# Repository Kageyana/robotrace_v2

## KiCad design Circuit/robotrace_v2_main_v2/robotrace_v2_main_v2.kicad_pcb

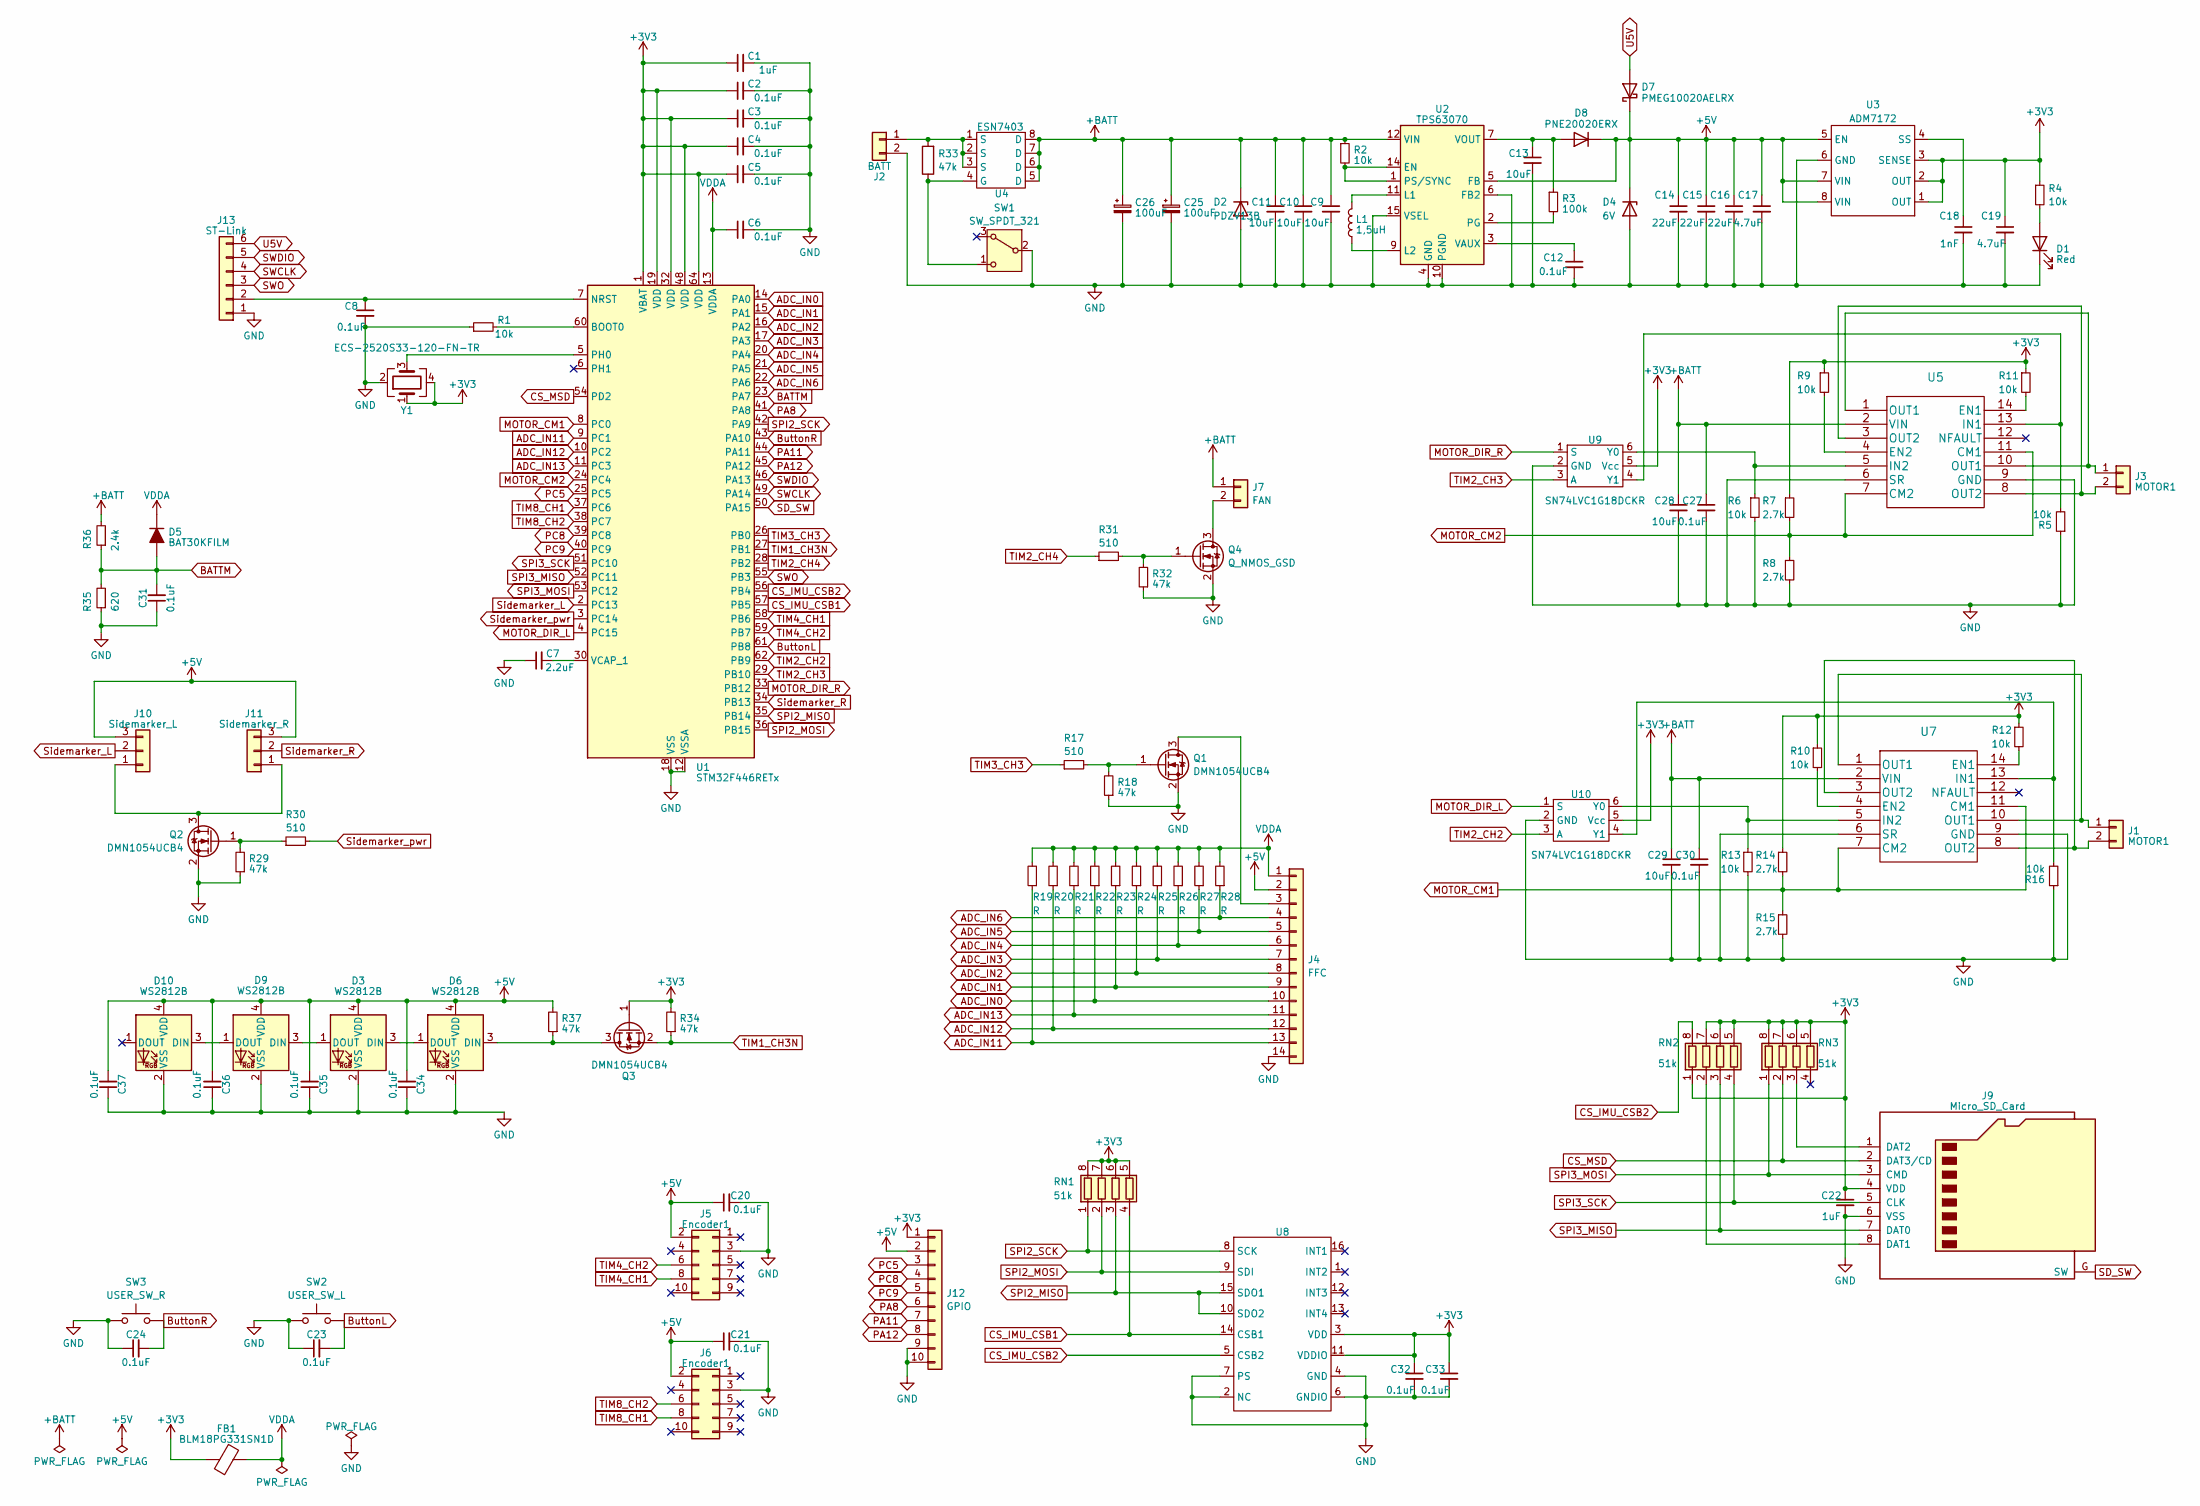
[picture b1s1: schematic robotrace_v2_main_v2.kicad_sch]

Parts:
C1, C22: 1uF; C_0402_1005Metric
C2, C3, C4, C5, C6, C8, C12, C20, C21, C23, C24, C27, C30, C31, C32, C33, C34, C35, C36, C37: 0.1uF; C_0402_1005Metric
C7: 2.2uF; C_0402_1005Metric_Pad0.74x0.62mm_HandSolder
C9, C10, C11: 10uF; C_0603_1608Metric_Pad1.08x0.95mm_HandSolder
C13: 10uF; C_0402_1005Metric
C14, C15, C16: 22uF; C_0805_2012Metric
C17, C19: 4.7uF; C_0402_1005Metric
C18: 1nF; C_0402_1005Metric
C25, C26: 100uF; CP_EIA-7343-15_Kemet-W
C28, C29: 10uF; C_0603_1608Metric
D1: Red; LED_0603_1608Metric_Pad1.05x0.95mm_HandSolder
D2: PDZV13B; D_SOD-128
D3, D6, D9, D10: WS2812B; WS2812C-2020
D4: 6V; D_SOD-123F
D5: BAT30KFILM; D_SOD-523
D7: PMEG10020AELRX; D_SOD-123W
D8: PNE20020ERX; D_SOD-123W
FB1: BLM18PG331SN1D; D_0603_1608Metric_Pad1.05x0.95mm_HandSolder
J1, J3: MOTOR1; Molex_mini-SPOX_1x02_P2.54mm_Horizontal
J2: BATT; Molex_mini-SPOX_1x02_P2.54mm_Horizontal
J4: FFC; Molex_FFC_1x14_P0.50mm_Horizontal
J5, J6: Encoder1; FTSH-105-01-F-D-K
J7: FAN; Molex_mini-SPOX_1x02_P2.54mm_Horizontal
J9: Micro_SD_Card; TF-SMD_TF-06A
J10: Sidemarker_L; JST_SH_BM03B-SRSS-TB_1x03-1MP_P1.00mm_Vertical
J11: Sidemarker_R; JST_SH_BM03B-SRSS-TB_1x03-1MP_P1.00mm_Vertical
J12: GPIO; Molex_FFC_1x10_P0.50mm_Horizontal
J13: ST-Link; JST_SH_BM06B-SRSS-TB_1x06-1MP_P1.00mm_Vertical
L1: 1,5uH; DFE252012P
Q1, Q2, Q3: DMN1054UCB4
Q4: Q_NMOS_GSD; SOT-23
R1, R2, R4: 10k; R_0402_1005Metric
R3: 100k; R_0402_1005Metric
R5, R6, R9, R10, R11, R12, R13, R16: 10k; R_0201_0603Metric
R7, R8, R14, R15: 2.7k; R_0402_1005Metric
R17, R30: 510; R_0201_0603Metric
R18, R29: 47k; R_0201_0603Metric
R19, R20, R21, R22, R23, R24, R25, R26, R27, R28: R; R_0603_1608Metric
R31: 510; R_0402_1005Metric
R32, R33, R34, R37: 47k; R_0402_1005Metric
R35: 620; R_0402_1005Metric
R36: 2.4k; R_0402_1005Metric
RN1, RN2, RN3: 51k; R_Array_Concave_4x0603
SW1: SW_SPDT_321; SS-1290
SW2: USER_SW_L; SKRPABE010
SW3: USER_SW_R; SKRPABE010
U1: STM32F446RETx; LQFP-64_10x10mm_P0.5mm
U2: TPS63070; Texas_TPS63070RNMR_EP2.6x3.1mm
U3: ADM7172; DFN-8_L3.0-W3.0-P0.50-BL-EP
U4: ESN7403; PDFN3x3-8L
U5, U7: MP6551GQB-P
U8: BMI088
U9, U10: SN74LVC1G18DCKR; Texas_R-PDSO-G6
Y1: ECS-2520S33-120-FN-TR; Oscillators_SMD_2.0x1.6

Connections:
+3V3: C1.1, C2.1, C3.1, C4.1, C5.1, C19.1, C22.1, C32.1, C33.1, FB1.2, J9.4 (VDD), J12.1, Q3.1 (G), R4.1, R7.1, R9.1, R10.1, R11.1, R12.1, R14.1, R34.2, RN1.5 (R4.2), RN1.6 (R3.2), RN1.7 (R2.2), RN1.8 (R1.2), RN2.1 (R1.1), RN2.5 (R4.2), RN2.6 (R3.2), RN2.7 (R2.2), RN3.5 (R4.2), RN3.6 (R3.2), RN3.7 (R2.2), RN3.8 (R1.2), U1.1 (VBAT), U1.19 (VDD), U1.32 (VDD), U1.48 (VDD), U1.64 (VDD), U3.1 (OUT), U3.2 (OUT), U3.3 (SENSE), U8.3 (VDD), U8.11 (VDDIO), U9.5 (Vcc), U10.5 (Vcc), Y1.1, Y1.4
+5V: C14.1, C15.1, C16.1, C17.1, C20.1, C21.1, C34.2, C35.2, C36.2, C37.2, D3.4 (VDD), D4.1 (K), D6.4 (VDD), D7.1 (K), D8.1 (K), D9.4 (VDD), D10.4 (VDD), J4.2, J5.2, J6.2, J10.3, J11.3, J12.2, R37.2, U2.5 (FB), U3.5 (EN), U3.7 (VIN), U3.8 (VIN)
+BATT: C9.1, C10.1, C11.1, C25.1, C26.1, C27.1, C28.1, C29.1, C30.1, D2.1 (K), J7.1, R2.1, R36.2, U2.12 (VIN), U2.13, U4.5 (D), U4.6 (D), U4.7 (D), U4.8 (D), U5.2 (VIN), U7.2 (VIN)
ADC_IN0: J4.10, R22.1, U1.14 (PA0)
ADC_IN1: J4.9, R23.1, U1.15 (PA1)
ADC_IN2: J4.8, R24.1, U1.16 (PA2)
ADC_IN3: J4.7, R25.1, U1.17 (PA3)
ADC_IN4: J4.6, R26.1, U1.20 (PA4)
ADC_IN5: J4.5, R27.1, U1.21 (PA5)
ADC_IN6: J4.4, R28.1, U1.22 (PA6)
ADC_IN11: J4.13, R19.1, U1.9 (PC1)
ADC_IN12: J4.12, R20.1, U1.10 (PC2)
ADC_IN13: J4.11, R21.1, U1.11 (PC3)
BATTM: C31.2, D5.2 (A), R35.2, R36.1, U1.23 (PA7)
ButtonL: C23.2, SW2.2, U1.61 (PB8)
ButtonR: C24.2, SW3.2, U1.43 (PA10)
CS_IMU_CSB1: RN1.4 (R4.1), U1.57 (PB5), U8.14 (CSB1)
CS_IMU_CSB2: RN2.8 (R1.2), U1.56 (PB4), U8.5 (CSB2)
CS_MSD: J9.2 (DAT3/CD), RN3.2 (R2.1), U1.54 (PD2)
GND: C1.2, C2.2, C3.2, C4.2, C5.2, C6.2, C7.1, C8.2, C9.2, C10.2, C11.2, C12.2, C13.2, C14.2, C15.2, C16.2, C17.2, C18.2, C19.2, C20.2, C21.2, C22.2, C23.1, C24.1, C25.2, C26.2, C27.2, C28.2, C29.2, C30.2, C31.1, C32.2, C33.2, C34.1, C35.1, C36.1, C37.1, D1.1 (K), D2.2 (A), D3.2 (VSS), D4.2 (A), D6.2 (VSS), D9.2 (VSS), D10.2 (VSS), J2.2, J4.14, J5.3, J6.3, J9.6 (VSS), J12.9, J12.10, J13.1, Q1.2 (S), Q2.2 (S), Q4.2 (S), R1.1, R5.1, R6.2, R8.2, R13.2, R15.2, R16.1, R18.1, R29.1, R32.1, R35.1, SW1.2 (B), SW2.1, SW3.1, U1.12 (VSSA), U1.18 (VSS), U1.31 (VSS), U1.47 (VSS), U1.63 (VSS), U2.4 (GND), U2.6 (FB2), U2.10 (PGND), U2.15 (VSEL), U3.6 (GND), U3.9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
MOTOR_CM1: R14.2, R15.1, U1.8 (PC0), U7.7 (CM2), U7.11 (CM1)
MOTOR_CM2: R7.2, R8.1, U1.24 (PC4), U5.7 (CM2), U5.11 (CM1)
MOTOR_DIR_L: U1.4 (PC15), U10.1 (S)
MOTOR_DIR_R: U1.33 (PB12), U9.1 (S)
unnamed: D1.2 (A), R4.2
unnamed: D3.3 (DIN), D6.1 (DOUT)
unnamed: D3.1 (DOUT), D9.3 (DIN)
unnamed: D6.3 (DIN), Q3.3 (D), R37.1
unnamed: C13.1, D8.2 (A), R3.1, U2.7 (VOUT), U2.8
unnamed: D9.1 (DOUT), D10.3 (DIN)
unnamed: J1.1, U7.1 (OUT1), U7.10 (OUT1)
unnamed: J1.2, U7.3 (OUT2), U7.8 (OUT2)
unnamed: J2.1, R33.2, U4.1 (S), U4.2 (S), U4.3 (S)
unnamed: J3.1, U5.1 (OUT1), U5.10 (OUT1)
unnamed: J3.2, U5.3 (OUT2), U5.8 (OUT2)
unnamed: J4.3, Q1.3 (D)
unnamed: J7.2, Q4.3 (D)
unnamed: J9.8 (DAT1), RN2.2 (R2.1)
unnamed: J9.1 (DAT2), RN3.3 (R3.1)
unnamed: J10.1, J11.1, Q2.3 (D)
unnamed: C8.1, J13.2, U1.7 (NRST)
unnamed: Q1.1 (G), R17.2, R18.2
unnamed: Q2.1 (G), R29.2, R30.1
unnamed: Q4.1 (G), R31.2, R32.2
unnamed: R33.1, SW1.1 (C), U4.4 (G)
unnamed: R1.2, U1.60 (BOOT0)
unnamed: U1.5 (PH0), Y1.3
unnamed: C7.2, U1.30 (VCAP_1)
unnamed: R2.2, U2.1 (PS/SYNC), U2.14 (EN)
unnamed: L1.2, U2.11 (L1)
unnamed: L1.1, U2.9 (L2)
unnamed: R3.2, U2.2 (PG)
unnamed: C12.1, U2.3 (VAUX)
unnamed: C18.1, U3.4 (SS)
unnamed: R11.2, U5.14 (EN1)
unnamed: R9.2, U5.4 (EN2)
unnamed: R5.2, U5.13 (IN1), U9.4 (Y1)
unnamed: R6.1, U5.5 (IN2), U9.6 (Y0)
unnamed: R12.2, U7.14 (EN1)
unnamed: R10.2, U7.4 (EN2)
unnamed: R13.1, U7.5 (IN2), U10.6 (Y0)
unnamed: R16.2, U7.13 (IN1), U10.4 (Y1)
PA8: J12.6, U1.41 (PA8)
PA11: J12.7, U1.44 (PA11)
PA12: J12.8, U1.45 (PA12)
PC5: J12.3, U1.25 (PC5)
PC8: J12.4, U1.39 (PC8)
PC9: J12.5, U1.40 (PC9)
SD_SW: J9.G (SW), U1.50 (PA15)
SPI2_MISO: RN1.3 (R3.1), U1.35 (PB14), U8.10 (SDO2), U8.15 (SDO1)
SPI2_MOSI: RN1.2 (R2.1), U1.36 (PB15), U8.9 (SDI)
SPI2_SCK: RN1.1 (R1.1), U1.42 (PA9), U8.8 (SCK)
SPI3_MISO: J9.7 (DAT0), RN2.3 (R3.1), U1.52 (PC11)
SPI3_MOSI: J9.3 (CMD), RN3.1 (R1.1), U1.53 (PC12)
SPI3_SCK: J9.5 (CLK), RN2.4 (R4.1), U1.51 (PC10)
SWCLK: J13.4, U1.49 (PA14)
SWDIO: J13.5, U1.46 (PA13)
SWO: J13.3, U1.55 (PB3)
Sidemarker_L: J10.2, U1.2 (PC13)
Sidemarker_R: J11.2, U1.34 (PB13)
Sidemarker_pwr: R30.2, U1.3 (PC14)
TIM1_CH3N: Q3.2 (S), R34.1, U1.27 (PB1)
TIM2_CH2: U1.62 (PB9), U10.3 (A)
TIM2_CH3: U1.29 (PB10), U9.3 (A)
TIM2_CH4: R31.1, U1.28 (PB2)
TIM3_CH3: R17.1, U1.26 (PB0)
TIM4_CH1: J5.8, U1.58 (PB6)
TIM4_CH2: J5.6, U1.59 (PB7)
TIM8_CH1: J6.8, U1.37 (PC6)
TIM8_CH2: J6.6, U1.38 (PC7)
U5V: D7.2 (A), J13.6
VDDA: C6.1, D5.1 (K), FB1.1, J4.1, R19.2, R20.2, R21.2, R22.2, R23.2, R24.2, R25.2, R26.2, R27.2, R28.2, U1.13 (VDDA)

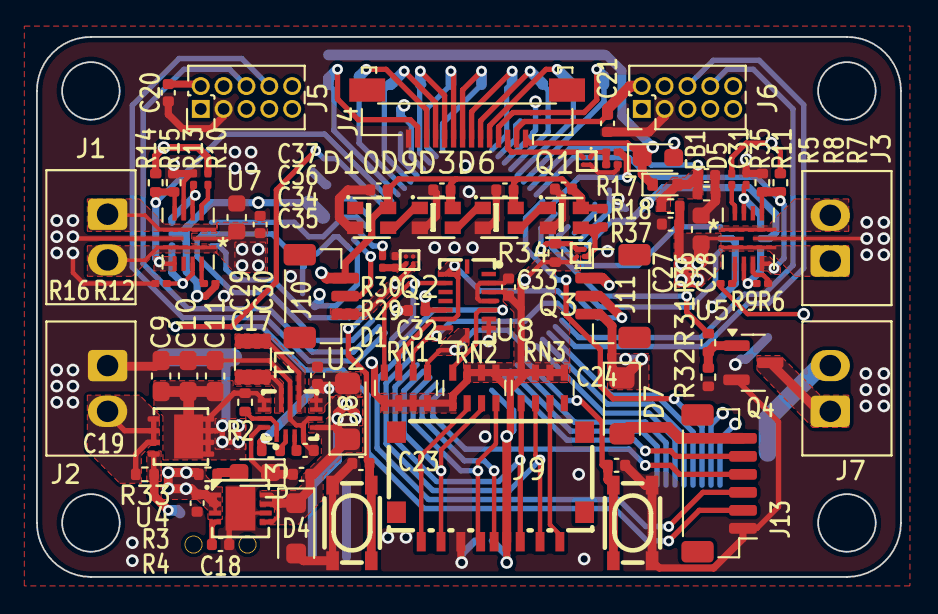
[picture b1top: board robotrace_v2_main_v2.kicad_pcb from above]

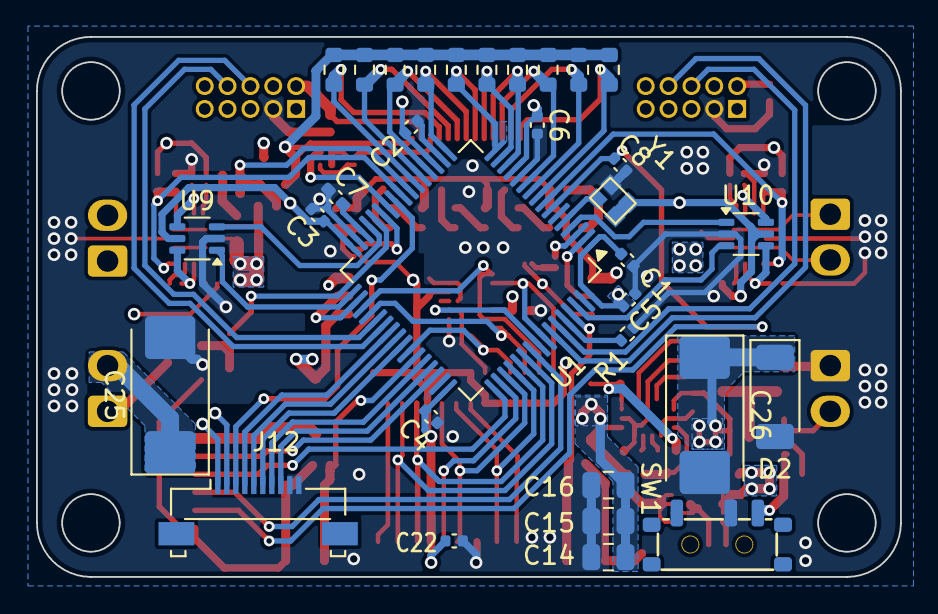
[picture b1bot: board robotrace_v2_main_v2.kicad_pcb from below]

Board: 4 copper layers, 48.0 x 30.0 mm, 118 parts (32 on the bottom side), 92 nets.

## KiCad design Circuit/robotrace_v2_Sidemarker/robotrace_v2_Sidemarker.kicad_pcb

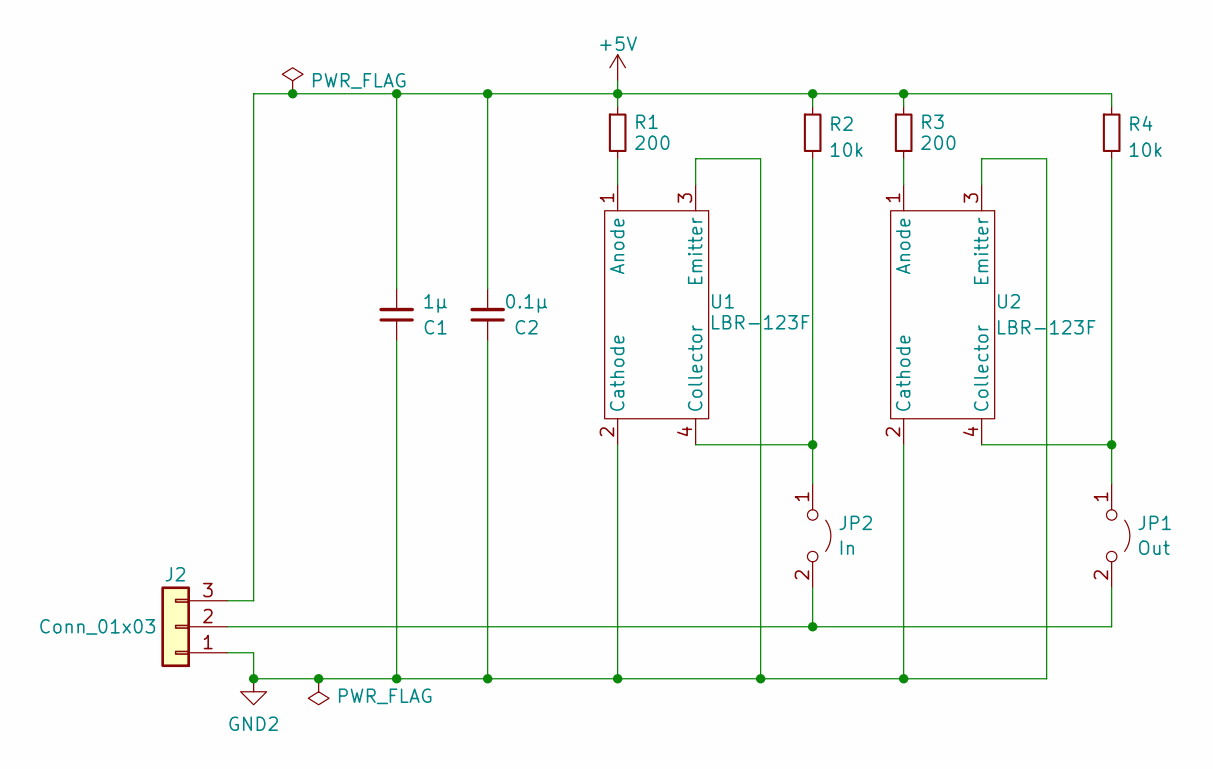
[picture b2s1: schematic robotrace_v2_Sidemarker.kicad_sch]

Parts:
C1: 1μ; C_0402_1005Metric_Pad0.74x0.62mm_HandSolder
C2: 0.1μ; C_0402_1005Metric_Pad0.74x0.62mm_HandSolder
J2: Conn_01x03; PinHeader_1x03_P2.00mm_Vertical
JP1: Out; SolderJumper-2_P1.3mm_Open_TrianglePad1.0x1.5mm
JP2: In; SolderJumper-2_P1.3mm_Open_TrianglePad1.0x1.5mm
R1, R3: 200; R_0603_1608Metric_Pad0.98x0.95mm_HandSolder
R2, R4: 10k; R_0603_1608Metric_Pad0.98x0.95mm_HandSolder
U1, U2: LBR-123F

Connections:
+5V: C1.2, C2.2, J2.3, R1.1, R2.1, R3.1, R4.1
GND2: C1.1, C2.1, J2.1, U1.2 (Cathode), U1.3 (Emitter), U2.2 (Cathode), U2.3 (Emitter)
unnamed: J2.2, JP1.2 (B), JP2.2 (B)
unnamed: JP1.1 (A), R4.2, U2.4 (Collector)
unnamed: JP2.1 (A), R2.2, U1.4 (Collector)
unnamed: R1.2, U1.1 (Anode)
unnamed: R3.2, U2.1 (Anode)

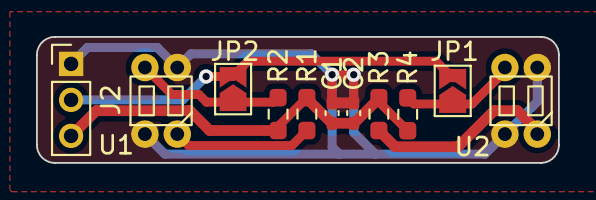
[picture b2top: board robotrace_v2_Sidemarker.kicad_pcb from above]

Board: 2 copper layers, 29.0 x 7.0 mm, 11 parts (0 on the bottom side), 7 nets.

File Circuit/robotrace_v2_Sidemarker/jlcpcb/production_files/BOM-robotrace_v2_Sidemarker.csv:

Comment,Designator,Footprint,LCSC
LBR-123F,U2,LBR-123F,
LBR-123F,U1,LBR-123F,
10k,R4,R_0603_1608Metric_Pad0.98x0.95mm_HandSolder,
200,R3,R_0603_1608Metric_Pad0.98x0.95mm_HandSolder,
Conn_01x03,J2,PinHeader_1x03_P2.00mm_Vertical,
200,R1,R_0603_1608Metric_Pad0.98x0.95mm_HandSolder,
0.1μ,C2,C_0402_1005Metric_Pad0.74x0.62mm_HandSolder,
1μ,C1,C_0402_1005Metric_Pad0.74x0.62mm_HandSolder,
10k,R2,R_0603_1608Metric_Pad0.98x0.95mm_HandSolder,

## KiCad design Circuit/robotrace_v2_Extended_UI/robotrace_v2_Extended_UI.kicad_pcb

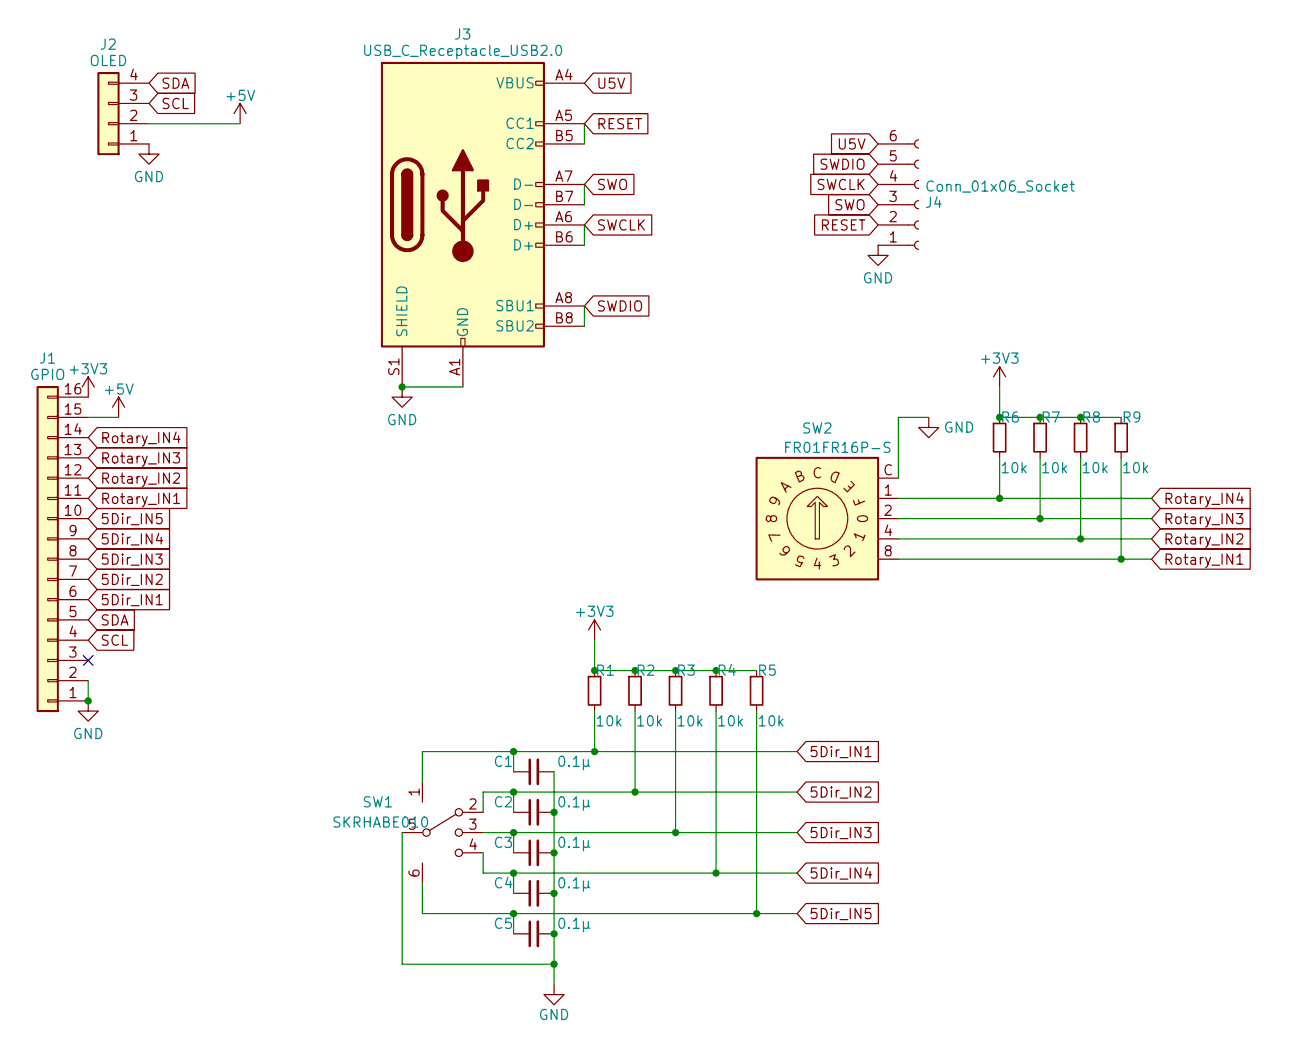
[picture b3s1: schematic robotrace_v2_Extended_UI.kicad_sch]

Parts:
C1, C2, C3, C4, C5: 0.1μ; C_0402_1005Metric_Pad0.74x0.62mm_HandSolder
J1: GPIO; Molex_FFC_1x16_P0.50mm_Horizontal
J2: OLED; PinHeader_1x04_P2.54mm_Vertical
J3: USB_C_Receptacle_USB2.0; USB_C_Receptacle_XKB_U262-16XN-4BVC11
J4: Conn_01x06_Socket; PinHeader_1x06_P1.27mm_Vertical
R1, R2, R3, R4, R5, R6, R7, R8, R9: 10k; R_0603_1608Metric_Pad0.98x0.95mm_HandSolder
SW1: SKRHABE010; SKRHAAE010
SW2: FR01FR16P-S

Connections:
5Dir_IN1: C1.1, J1.6, R1.2, SW1.1
5Dir_IN2: C2.1, J1.7, R2.2, SW1.2
5Dir_IN3: C3.1, J1.8, R3.2, SW1.3
5Dir_IN4: C4.1, J1.9, R4.2, SW1.4
5Dir_IN5: C5.1, J1.10, R5.2, SW1.6
+3V3: J1.16, R1.1, R2.1, R3.1, R4.1, R5.1, R6.1, R7.1, R8.1, R9.1
+5V: J1.15, J2.2
GND: C1.2, C2.2, C3.2, C4.2, C5.2, J1.1, J1.2, J2.1, J3.A1 (GND), J3.A12 (GND), J3.B1 (GND), J3.B12 (GND), J3.S1 (SHIELD), J4.1, SW1.5, SW2.C
RESET: J3.A5 (CC1), J3.B5 (CC2), J4.2
Rotary_IN1: J1.11, R9.2, SW2.8
Rotary_IN2: J1.12, R8.2, SW2.4
Rotary_IN3: J1.13, R7.2, SW2.2
Rotary_IN4: J1.14, R6.2, SW2.1
SCL: J1.4, J2.3
SDA: J1.5, J2.4
SWCLK: J3.A6 (D+), J3.B6 (D+), J4.4
SWDIO: J3.A8 (SBU1), J3.B8 (SBU2), J4.5
SWO: J3.A7 (D-), J3.B7 (D-), J4.3
U5V: J3.A4 (VBUS), J3.A9 (VBUS), J3.B4 (VBUS), J3.B9 (VBUS), J4.6

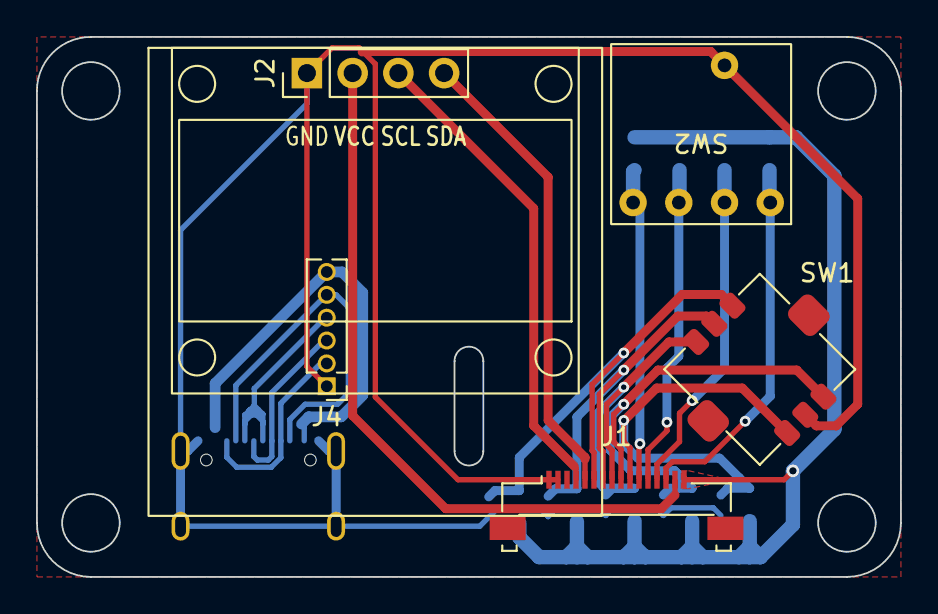
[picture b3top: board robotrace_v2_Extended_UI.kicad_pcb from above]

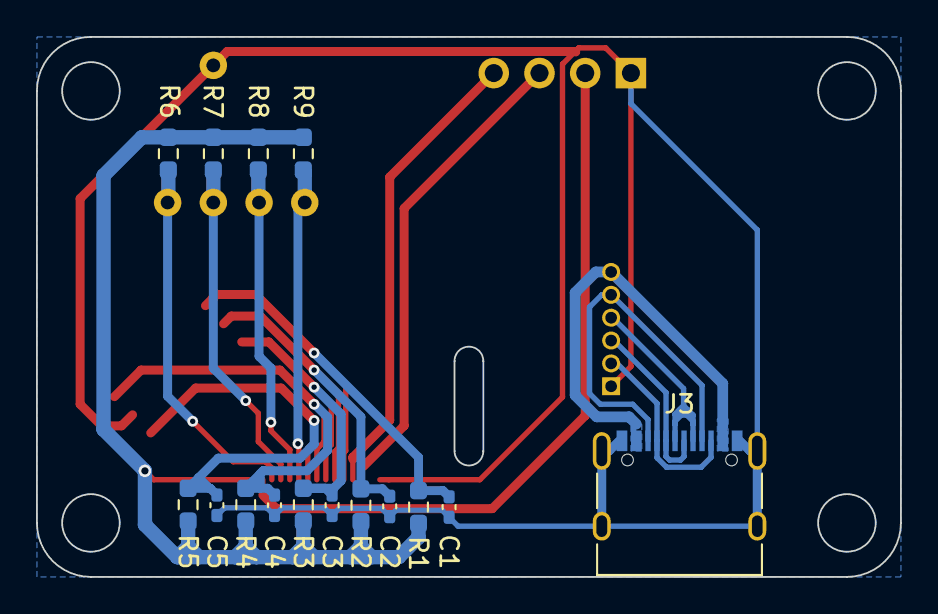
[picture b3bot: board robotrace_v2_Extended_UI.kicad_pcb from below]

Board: 2 copper layers, 48.0 x 30.0 mm, 20 parts (15 on the bottom side), 19 nets.

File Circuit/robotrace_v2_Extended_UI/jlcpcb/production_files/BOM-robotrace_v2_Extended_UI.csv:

Comment,Designator,Footprint,LCSC
OLED,J2,PinHeader_1x04_P2.54mm_Vertical,
GPIO,J1,Molex_FFC_1x16_P0.50mm_Horizontal,
10k,R1,R_0603_1608Metric_Pad0.98x0.95mm_HandSolder,
10k,R9,R_0603_1608Metric_Pad0.98x0.95mm_HandSolder,
10k,R3,R_0603_1608Metric_Pad0.98x0.95mm_HandSolder,
10k,R5,R_0603_1608Metric_Pad0.98x0.95mm_HandSolder,
10k,R8,R_0603_1608Metric_Pad0.98x0.95mm_HandSolder,
0.1μ,C3,C_0402_1005Metric_Pad0.74x0.62mm_HandSolder,
USB_C_Receptacle_USB2.0,J3,USB_C_Receptacle_XKB_U262-16XN-4BVC11,
10k,R7,R_0603_1608Metric_Pad0.98x0.95mm_HandSolder,
0.1μ,C2,C_0402_1005Metric_Pad0.74x0.62mm_HandSolder,
10k,R4,R_0603_1608Metric_Pad0.98x0.95mm_HandSolder,
Conn_01x06_Socket,J4,PinHeader_1x06_P1.27mm_Vertical,
0.1μ,C1,C_0402_1005Metric_Pad0.74x0.62mm_HandSolder,
10k,R2,R_0603_1608Metric_Pad0.98x0.95mm_HandSolder,
0.1μ,C5,C_0402_1005Metric_Pad0.74x0.62mm_HandSolder,
10k,R6,R_0603_1608Metric_Pad0.98x0.95mm_HandSolder,
0.1μ,C4,C_0402_1005Metric_Pad0.74x0.62mm_HandSolder,
SKRHABE010,SW1,SKRHAAE010,
FR01FR16P-S,SW2,FR01FR16P-S,

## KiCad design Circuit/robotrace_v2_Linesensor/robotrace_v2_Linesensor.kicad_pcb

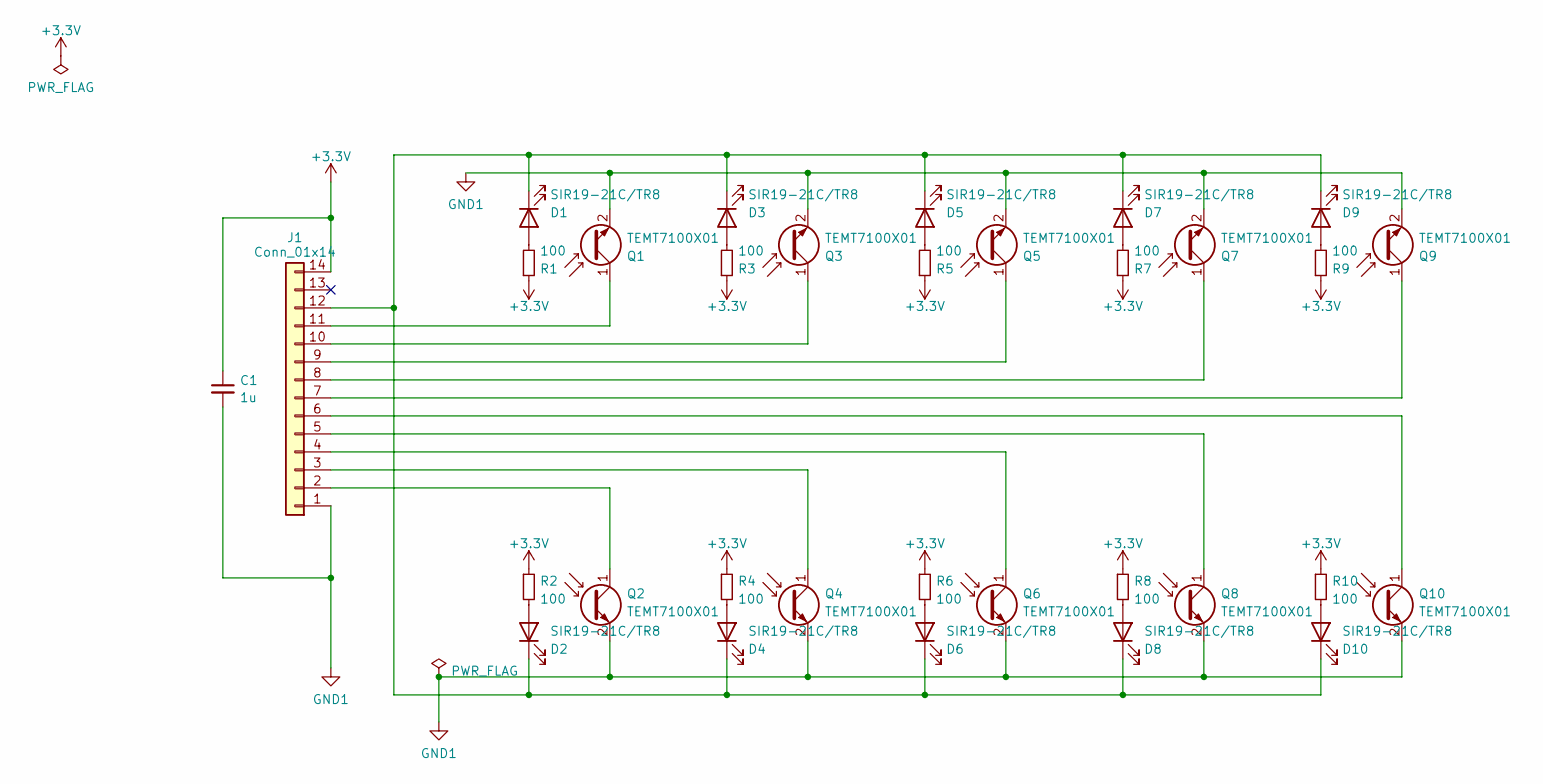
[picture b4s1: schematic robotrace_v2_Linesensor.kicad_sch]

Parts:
C1: 1u; C_0402_1005Metric_Pad0.74x0.62mm_HandSolder
D1, D2, D3, D4, D5, D6, D7, D8, D9, D10: SIR19-21C/TR8; LED_0603_1608Metric_Pad1.05x0.95mm_HandSolder
J1: Conn_01x14; Molex_FFC_1x14_P0.50mm_Horizontal
Q1, Q2, Q3, Q4, Q5, Q6, Q7, Q8, Q9, Q10: TEMT7100X01; LED_0805_2012Metric_Pad1.15x1.40mm_HandSolder
R1, R2, R3, R4, R5, R6, R7, R8, R9, R10: 100; R_0603_1608Metric_Pad0.98x0.95mm_HandSolder

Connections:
+3V3: C1.1, J1.14, R1.1, R2.1, R3.1, R4.1, R5.1, R6.1, R7.1, R8.1, R9.1, R10.1
GND1: C1.2, J1.1, Q1.2 (E), Q2.2 (E), Q3.2 (E), Q4.2 (E), Q5.2 (E), Q6.2 (E), Q7.2 (E), Q8.2 (E), Q9.2 (E), Q10.2 (E)
unnamed: D1.2 (A), R1.2
unnamed: D1.1 (K), D2.1 (K), D3.1 (K), D4.1 (K), D5.1 (K), D6.1 (K), D7.1 (K), D8.1 (K), D9.1 (K), D10.1 (K), J1.12
unnamed: D2.2 (A), R2.2
unnamed: D3.2 (A), R3.2
unnamed: D4.2 (A), R4.2
unnamed: D5.2 (A), R5.2
unnamed: D6.2 (A), R6.2
unnamed: D7.2 (A), R7.2
unnamed: D8.2 (A), R8.2
unnamed: D9.2 (A), R9.2
unnamed: D10.2 (A), R10.2
unnamed: J1.2, Q2.1 (C)
unnamed: J1.3, Q4.1 (C)
unnamed: J1.4, Q6.1 (C)
unnamed: J1.5, Q8.1 (C)
unnamed: J1.6, Q10.1 (C)
unnamed: J1.7, Q9.1 (C)
unnamed: J1.8, Q7.1 (C)
unnamed: J1.9, Q5.1 (C)
unnamed: J1.10, Q3.1 (C)
unnamed: J1.11, Q1.1 (C)

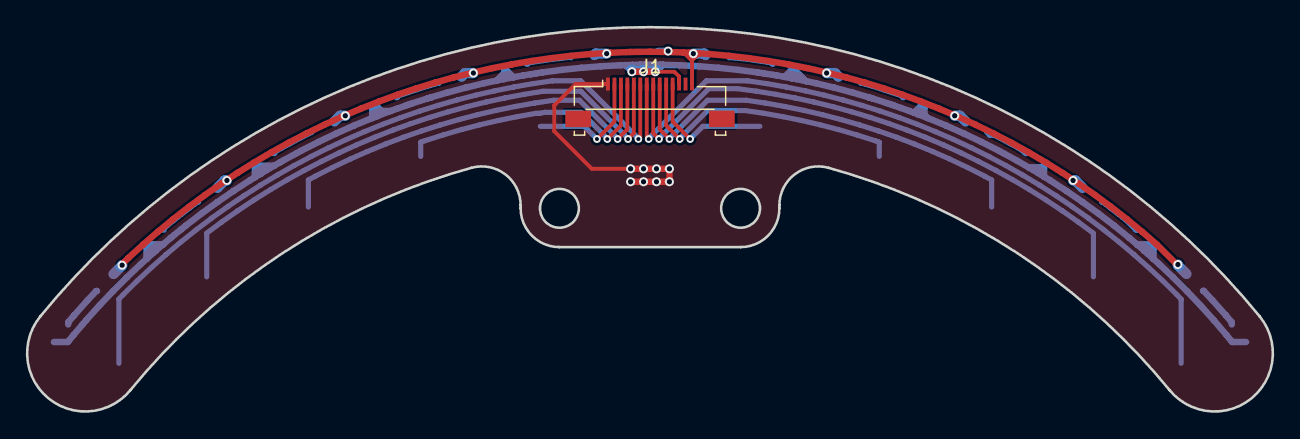
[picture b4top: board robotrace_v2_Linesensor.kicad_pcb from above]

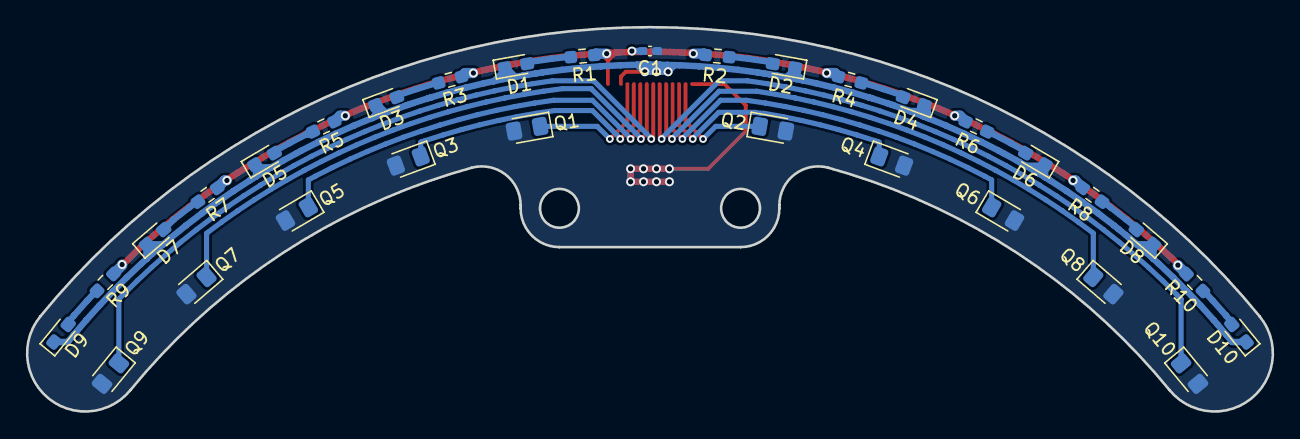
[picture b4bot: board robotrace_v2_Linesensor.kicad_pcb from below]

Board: 2 copper layers, 96.3 x 29.7 mm, 32 parts (31 on the bottom side), 23 nets.

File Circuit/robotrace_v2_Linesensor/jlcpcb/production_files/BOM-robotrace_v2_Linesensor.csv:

Comment,Designator,Footprint,LCSC
SIR19-21C/TR8,"D1,D10,D2,D3,D4,D5,D6,D7,D8,D9",LED_0603_1608Metric_Pad1.05x0.95mm_HandSolder,C114576
TEMT7100X01,"Q1,Q10,Q2,Q3,Q4,Q5,Q6,Q7,Q8,Q9",LED_0805_2012Metric_Pad1.15x1.40mm_HandSolder,C144928
100,"R1,R10,R2,R3,R4,R5,R6,R7,R8,R9",R_0603_1608Metric_Pad0.98x0.95mm_HandSolder,C22787
1μ,C1,C_0402_1005Metric_Pad0.74x0.62mm_HandSolder,C52923
Conn_01x14,J1,Molex_FFC_1x14_P0.50mm_Horizontal,

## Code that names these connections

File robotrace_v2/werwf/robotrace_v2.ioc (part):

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Mcu.Name=STM32F446R(C-E)Tx
Mcu.Package=LQFP64
Mcu.UserName=STM32F446RETx
PA0-WKUP.Signal=ADCx_IN0
PA1.Signal=ADCx_IN1
PA10.GPIOParameters=GPIO_PuPd,GPIO_Label
PA10.GPIO_Label=ButtonR
PA10.GPIO_PuPd=GPIO_PULLUP
PA10.Signal=GPIO_Input
PA11.GPIOParameters=PinState
PA11.PinState=GPIO_PIN_SET
PA11.Signal=GPIO_Output
PA12.GPIOParameters=PinState
PA12.PinState=GPIO_PIN_SET
PA12.Signal=GPIO_Output
PA13.Mode=Trace_Asynchronous_SW
PA13.Signal=SYS_JTMS-SWDIO
PA14.Mode=Trace_Asynchronous_SW
PA14.Signal=SYS_JTCK-SWCLK
PA15.GPIOParameters=GPIO_PuPd,GPIO_Label
PA15.GPIO_Label=SD_SW
PA15.GPIO_PuPd=GPIO_PULLDOWN
PA15.Signal=GPIO_Input
PA2.Signal=ADCx_IN2
PA3.Signal=ADCx_IN3
PA4.Signal=ADCx_IN4
PA5.Signal=ADCx_IN5
PA6.Signal=ADCx_IN6
PA7.GPIOParameters=GPIO_Label
PA7.GPIO_Label=BATTM
PA7.Signal=ADCx_IN7
PA8.Mode=I2C
PA8.Signal=I2C3_SCL
PA9.Mode=Full_Duplex_Master
PA9.Signal=SPI2_SCK
PB0.Signal=S_TIM3_CH3
PB1.GPIOParameters=GPIO_Speed,GPIO_PuPd
PB1.GPIO_PuPd=GPIO_PULLDOWN
PB1.GPIO_Speed=GPIO_SPEED_FREQ_HIGH
PB1.Mode=PWM Generation3 CH3N
PB1.Signal=TIM1_CH3N
PB10.Signal=S_TIM2_CH3
PB12.GPIOParameters=GPIO_Label
PB12.GPIO_Label=MOTOR_DIR_R
PB12.Signal=GPIO_Output
PB13.GPIOParameters=GPIO_Label
PB13.GPIO_Label=SIDEMARKER_R
PB13.Signal=GPIO_Input
PB14.Mode=Full_Duplex_Master
PB14.Signal=SPI2_MISO
PB15.Mode=Full_Duplex_Master
PB15.Signal=SPI2_MOSI
PB2.Signal=S_TIM2_CH4
PB3.Mode=Trace_Asynchronous_SW
PB3.Signal=SYS_JTDO-SWO
PB4.GPIOParameters=PinState,GPIO_Label
PB4.GPIO_Label=IMU_CSB2
PB4.PinState=GPIO_PIN_SET
PB4.Signal=GPIO_Output
PB5.GPIOParameters=PinState,GPIO_Label
PB5.GPIO_Label=IMU_CSB1
PB5.PinState=GPIO_PIN_SET
PB5.Signal=GPIO_Output
PB6.Signal=S_TIM4_CH1
PB7.Signal=S_TIM4_CH2
PB8.GPIOParameters=GPIO_PuPd,GPIO_Label
PB8.GPIO_Label=ButtonL
PB8.GPIO_PuPd=GPIO_PULLUP
PB8.Signal=GPIO_Input
PB9.Signal=S_TIM2_CH2
PC0.GPIOParameters=GPIO_Label
PC0.GPIO_Label=MOTOR_CM1
PC0.Signal=ADCx_IN10
PC1.Signal=ADCx_IN11
PC10.Mode=Full_Duplex_Master
PC10.Signal=SPI3_SCK
PC11.Mode=Full_Duplex_Master
PC11.Signal=SPI3_MISO
PC12.Mode=Full_Duplex_Master
PC12.Signal=SPI3_MOSI
PC13.GPIOParameters=GPIO_Label
PC13.GPIO_Label=SIDEMARKER_L
PC13.Signal=GPIO_Input
PC14-OSC32_IN.GPIOParameters=PinState,GPIO_Label
PC14-OSC32_IN.GPIO_Label=SidemarkerPWR
PC14-OSC32_IN.PinState=GPIO_PIN_SET
PC14-OSC32_IN.Signal=GPIO_Output
PC15-OSC32_OUT.GPIOParameters=GPIO_Label
PC15-OSC32_OUT.GPIO_Label=MOTOR_DIR_L
PC15-OSC32_OUT.PinState=GPIO_PIN_RESET
PC15-OSC32_OUT.Signal=GPIO_Output
PC2.Signal=ADCx_IN12
PC3.Signal=ADCx_IN13
PC4.GPIOParameters=GPIO_Label
PC4.GPIO_Label=MOTOR_CM2
PC4.Signal=ADCx_IN14
PC5.Signal=ADCx_IN15
PC6.Signal=S_TIM8_CH1
PC7.Signal=S_TIM8_CH2
PC8.Signal=GPIO_Output
PC9.Mode=I2C
PC9.Signal=I2C3_SDA
PD2.GPIOParameters=PinState,GPIO_Label
PD2.GPIO_Label=CS_MSD
PD2.PinState=GPIO_PIN_SET
PD2.Signal=GPIO_Output
PH0-OSC_IN.Mode=HSE-External-Oscillator
PH0-OSC_IN.Signal=RCC_OSC_IN
PH1-OSC_OUT.Mode=HSE-External-Oscillator
PH1-OSC_OUT.Signal=RCC_OSC_OUT
RCC.HSE_VALUE=12000000
RCC.SYSCLKFreq_VALUE=180000000
RCC.SYSCLKSource=RCC_SYSCLKSOURCE_PLLCLK
board=custom

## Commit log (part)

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2025-11-02 vscode拡張機能アップデート
2025-11-03 緊急停止条件を修正
2025-11-05 AD変換遅延処理が正しい秒数で遅延しない問題を修正
2025-11-07 PID制御の安定性向上 光変調高速化
2025-11-07 機体3Dモデルを追加
2025-11-08 マーカーセンサの光変調実装
2025-11-08 光変調周波数10kHz
2025-11-09 光変調周波数5kHz
2025-11-09 光変調周波数2kHz
2025-11-09 マーカーセンサがオフにならない問題を修正
2025-11-10 ライントレース制御に角速度FBを追加
2025-11-11 ソフトウェアリセット時にログが保存できない問題を修正
2025-11-15 ソフトウェアリセット後にマーカーを検知できない区間がある問題を修正
2025-11-15 PIDゲイン初期値を現状のゲインに変更
2025-11-15 オートスタートの2走目移行にマーカーが読めない問題を修正
2025-11-22 不要処理を停止するようにした
2025-11-22 1次走行用のゲインを用意
2025-11-22 ゲイン修正
2025-11-23 クロスライン通過時にPゲインを下げて機体がブレないようにした
2025-11-24 ログに電流値を追加
2025-11-24 クロスライン通過時のゲインを変更
2025-11-24 ログが400個以上でソフトウェアリセットが機能しなくなる問題を解決
2025-11-24 ログファイルが300以上のときファイル数過多の警告を出すようにした
2025-11-24 不要変数、警告を削減のため型変更
2025-11-25 Add angular smoothing to target speed calculation
2025-11-25 角速度平滑化のコメント追加とインデント修正
2025-11-26 目標速度平滑化結果のCSV出力を追加
2025-11-26 SDカード書き込み処理のフォーマット修正
2025-11-26 コメント補足とフォーマット整備
2025-12-05 回路図を最新版に更新
2025-12-05 回路図pdf更新
2025-12-05 加速度センサを有効化 SPI通信速度を11.25MBits/sに制限
2025-12-06 X,Y加速度をログに保存するようにした
2025-12-06 BMI088の加速度キャリブレーションを追加
2025-12-06 コメント整理
2025-12-07 速度計算関数追加
2025-12-07 重力基準を保持する加速度キャリブレーション修正
2025-12-07 Fix calibrationIMU closing brace
2025-12-12 スリップ検出機能の追加と関連パラメータの定義を行い、ログ出力にスリップ情報を追加
2025-12-13 1次走行のゲインを修正
2025-12-13 スリップ検出に使う加速度をyaw軸角速度で補正した
2025-12-14 ライン追跡制御から角速度成分を除外
2025-12-14 クロスライン距離の定義を変更し、SDカードのログ出力を更新。緊急停止条件を調整し、タイマーのログ出力を改善。角速度FBライントレースの目標値を現在値とスケールを合わせた
2025-12-14 SDカードのログ出力を更新し、角速度制御のパラメータを調整。クロスライン検出の状態管理を改善。
2025-12-15 SDカードのログ出力のバッファサイズを更新し、緊急停止条件を改善。ラインセンサの状態管理を強化。
2025-12-17 マーカー処理状態をクリアする関数を追加。緊急停止条件のラインセンサーのカウントを明確に分け、関連する変数名を更新。
2025-12-18 エラー修正
2025-12-18 ログ出力の加速度パラメータを更新し、スリップ検出のサンプリングウィンドウを短縮。IMU初期化状態に基づくスリップ検出の条件を改善。
2025-12-20 SDカードのログ出力設定を更新し、センサ値のログ出力を整理。マーカーセンサ処理状態をクリアする関数を追加し、緊急停止フラグの管理を改善。
2025-12-20 ログヘッダーに新しい関数を追加し、制御パラメータを記録する機能を強化
2025-12-21 ヘッダにパラメータ追加
2025-12-24 ログヘッダーに制御パラメータを追加し、フォーマットを修正
2025-12-24 緊急停止処理を改善し、機体停止時の速度制御を追加
2025-12-24 クロスライン検出機能を追加し、関連する定義を整理。緊急停止処理におけるクロスライン状態の管理を改善。
2025-12-25 速度パラメータを調整し、クロスライン検出状態の変数名を変更。
2025-12-27 ログ用の速度制御iP成分とフィードフォワード成分を追加し、SDカードのログ出力を更新。PWM制限を1000に修正。
2025-12-27 ライントレース制御正規化の変更を取り消し
2025-12-28 左右モーターの独立制御を追加し、速度制御ゲインを同期。ターゲット速度に基づくPWM出力を調整。
2025-12-29 制御ループ内のコメントアウトされたコードを整理し、モーター出力の呼び出しを修正。タイマー割り込みでのモーター制御速度の更新を追加。
2025-12-29 ログ用の速度制御iP成分とフィードフォワード成分を削除し、SDカードのログ出力を更新。ライン制御と速度制御の処理を整理。直線時にゲインを下げるようにした
2025-12-29 速度計画ログ出力のフラグを追加し、SDカードへの記録処理を条件付きで実行するように修正
2025-12-29 速度パラメータの変更、ROCに基づくゲイン切り替えの実装、SDカードログ出力の更新
2025-12-29 SDカードログ出力の構成を修正し、加速度値を追加。タイマー割り込みでのログ出力を更新。
2025-12-30 スリップ検出パラメータを更新し、IMUおよびエンコーダの加速度処理を改善。ログ出力にターゲット速度を追加。
2025-12-30 スリップ検出の閾値を追加し、関連するログ出力を更新。SDカードのログサイズを調整し、FATFSのexFATサポートを有効化。
2025-12-30 一時ファイル終了処理を追加し、スリップ指標のLPF係数を変更。ログ保存処理を改善し、FATFSのロック設定を更新。
2026-01-02 スリップ検出の閾値を更新し、ログ出力の浮動小数点数の数を減少。SDカードへのログ出力処理を改善。
2026-01-02 Add lateral slip detection and logging
2026-01-02 Separate longitudinal and lateral slip metrics
2026-01-02 Adjust slip low-accel gating and logging
2026-01-04 関数名をcheckROCからchangeGainに変更し、ROCに応じたゲイン切り替え処理を明確化
2026-01-04 SDカードログの設定を更新し、lineTraceCtrl.kpのログを追加
2026-01-04 ソフトリセットの再実行に対応
2026-01-04 Fix reset gain state in PID control
2026-01-05 Interrupt1ms関数内のupdateSlipDetection呼び出しを重複削除
2026-01-07 SDカードおよびバッテリー管理のロギング機能を改善し、ADC設定を更新 ADCの基準電圧をVrefintから取得
2026-01-08 モーター電流センサのキャリブレーション機能を追加し、ADCサンプリング時間を短縮
2026-01-08 MOTOR_AD_WINDOWの値を64から32に変更し、モーター電流の移動平均計算を最適化
2026-01-10 スリップ検出機能にモータ電流によるノイズ補正を追加し、関連する定数を定義。motor.cのデータ型を修正。
2026-01-10 横スリップ検出の惰性ゲート追加
2026-01-11 横スリップ検出の初期化と電流LPF整理
2026-01-11 PWM LPF定数追加と重複include修正
2026-01-11 電流LPF係数と補正ゲインの値を調整し、閾値スケール上限を更新
2026-01-11 スリップ検出の電流条件付き整理
2026-01-11 横スリップゲートの分岐整理
2026-01-11 ヒステリシス更新のカウンタ初期化
2026-01-12 距離補正スケールとログを追加
2026-01-12 距離補正を常時有効にする
2026-01-12 BMI088.hのCOEFF_DPDを-0.996Fに修正し、SDcard.cのログヘッダーのサイズを2048に増加、control.cのスリップ距離補正パラメータを微調整、setup.cの加速度パラメータの最大値を20.0に変更
2026-01-13 1msカウンタ更新の条件整理
2026-01-14 スタートリセット完了待ち制御
2026-01-14 パルス補正ログ列を追加
2026-01-14 スタートリセットACK待ち追加
2026-01-14 距離ログのパルス版整理
2026-01-15 スタートリセットACKとログ引数整合
2026-01-15 ログ列名と型整合を修正
2026-01-17 スタート通過時リセットを割り込みで実施
2026-01-17 スタートリセット要求APIを削除
2026-01-17 スタート通過時にカウンタ初期化
2026-01-17 マーカー補正のパルス同期を追加
2026-01-17 スリップ距離補正パラメータを追加し、関連する未使用の変数を削除
2026-01-17 スリップ検出の閾値管理を整理
2026-01-17 スリップ距離補正パラメータの追加と関連する変数の整理、ログ出力の修正
2026-01-17 スリップ検出パラメータの調整と関連する関数の修正
2026-01-17 横滑り判定の早期化対応
2026-01-17 横滑り判定の電流ゲート追加
2026-01-17 横滑りON判定の瞬時電流ゲート化
2026-01-17 横滑りON判定の瞬時ゲート整理
2026-01-17 横滑りON判定の連続電流ゲート追加
2026-01-18 横滑りON判定の瞬時電流和の下限を0.25Aから0.50Aに変更し、スリップ距離補正処理のIRQ管理を削除
2026-01-18 緊急停止処理のモータ停止タイミングを変更
2026-01-18 スリップ距離補正機能の強化とエンコーダ補正の追加 - LOG_NUM_32BITを4から5に変更 - スリップ距離補正パラメータの調整 - calcXYcie関数の引数を変更 - 補正後の現在速度を管理するencCurrentCorr_pを追加 - ログ出力にencCurrentCorr_pを追加
2026-01-18 パラメータ変更して誤検知現減少
2026-01-19 前後速度の融合推定を追加
2026-01-21 Use encPulse for slip distance
2026-01-21 Fix speed units in slip analysis
2026-01-21 スリップ解析の速度単位を修正
2026-01-22 ログ作成時の一覧更新を追加
2026-01-24 ログ保存後の自動解析更新を安全化
2026-01-24 ログ保存成否判定の条件を修正
2026-01-24 パラメータ更新
2026-01-24 スタートマーカー検出のロジックを改善
2026-01-24 パラメータ修正
2026-01-24 ログ記録のスキーマを導入し、ログバッファの書き込み処理を簡素化
2026-01-24 ログの順番を変更
2026-01-25 ゴールマーカーの読み取り回数を3から5に変更し、速度計画ログの書き出し機能を追加
2026-01-25 SD読み取りのデバッグ情報を追加し、ログ記録処理を改善
2026-01-26 問題は解決していません。 SDカード関連の機能を強化し、ロック機能を追加。セクター数取得機能を実装し、エラーハンドリングを改善。
2026-01-30 fix: ?????SD????I/O????
    - ????????????????
    - readLogDistance/Slip???????1????????
    - FatFs????try_lock??IRQ???
    - CSD???????????????
    - CTRL_SYNC?SD_Sync???
    - ????????????????????1??
2026-01-30 ログを走行中書き込み専用に統一
    - LOG_RUNNING_WRITE の条件分岐を撤去
    - 走行中書き込みの経路に整理
    - 未定義時の処理を削除
2026-01-31 feat: SDカードのログバッファ管理を改善し、フラッシュ処理を追加
2026-01-31 fix: ゴールマーカーの読み取り回数を2回に変更し、移動距離計算関数を追加
2026-01-31 fix: calcDlMm関数を速度と経過時間に基づいて移動距離を算出するように修正し、ROCの閾値を更新
2026-02-01 fix: ゴールマーカーの読み取り回数を5回に変更し、ラインセンサの外れ判定を150に更新 feat: 直線判定の状態を管理するための変数を追加し、関連するロジックを実装
2026-02-04 fix: ゴールマーカーの読み取り回数を3回に変更し、スリップ解析の閾値を更新
2026-02-06 feat: ログ番号管理機能を追加し、保存済みログ番号の読み書きを実装 一定数でログを削除する機能を追加
2026-02-11 SDカードの安定性向上
2026-02-11 fix: ゴールマーカーの読み取り回数を2回に変更し、曲率半径計算用変数を追加
2026-02-14 fix: 曲率半径の閾値を800mmに変更し、マーカー探索幅を拡大
2026-02-15 先行減速距離のパラメータを追加し、関連する関数を実装
2026-02-15 ゲイン変更関連のパラメータを追加し、直線判定の閾値を修正 直線、カーブのゲイン切り替え処理を距離で判定するように変更
2026-02-15 fix: PID制御用ゲインとセンサ重み係数の調整、カーブ用ゲインの条件を変更
2026-02-15 曲率半径の閾値を統一し、ゲイン変更処理を改善
2026-02-17 距離補正関連の定数をヘッダに移動、エンコーダのカウント取得処理を整理
2026-02-18 ゲイン変更関連のパラメータを追加し、カーブ進入と復帰判定の処理を改善
2026-02-18 速度制御処理を最適化し、ショートカット走行時の動作を改善
2026-02-18 calcXYcies関数に処理内容のコメント追加
2026-02-20 ショートカット機能の改善と最適化インデックス更新処理の追加
2026-02-21 ゴールマーカーの読み取り回数を変更し、カーブおよび直線用ゲイン切替えの閾値を調整
2026-02-22 ショートカット関連のパラメータを調整し、緊急停止条件を変更
2026-02-22 ショートカット走行時の先読み距離を150mmに変更し、XY座標計算での三角関数を最適化
2026-02-23 カウントダウン時間を5000から2000に変更
2026-03-07 BMI088valからimuValへのIMU変数使用の再構成
    - emergencyStop.c内のジャイロ値参照を更新し、imuValを使用するように変更。
    - setup.c内の角度および加速度参照をBMI088valからimuValに変更。
    - timer.c内の温度割り当てを調整し、BMI088val.tempをimuVal.tempに格納するように変更。
2026-03-14 IMU関連の定数と関数を移動し、旋回中心補正機能を実装
2026-03-21 スリップ検出機能の改善とログ出力の拡張 - スリップ判定の有効条件とカウント許可条件を追加 - スリップ関連の新しいデータをログに記録 - スリップ判定の初期化処理を修正
2026-06-28 docs: add AGENTS and robotrace skills
2026-06-28 .gitignoreにanaliysisディレクトリを追加し、PIDcontrol.hのホイール径を24.0fから23.5fに修正、SDcard.cにautoStartとemcStopのログ出力を追加、timer.cのタイマー割り込みの概要を更新
2026-06-28 Normalize typo-derived names
2026-06-28 コミットメッセージ方針を追記
2026-06-28 未実装タスクのログ情報と設定修復を実装
2026-06-28 バッテリ電圧の異常値を修正
2026-06-30 スリップ検出の低負荷誤検出を抑制

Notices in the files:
parts and their libraries:
Copyright 2021 Accelerated Designs. All rights reserved.
